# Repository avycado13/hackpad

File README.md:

# hackpad
my hackpad that i can use for various controls

## Features
- 15 buttons in a 3x5 matrix
- 3 rotary encoders for controls like volume and numeric input
- an oled screen to show preset in action and other details
- 3 status leds
- maybe games on the device itself?

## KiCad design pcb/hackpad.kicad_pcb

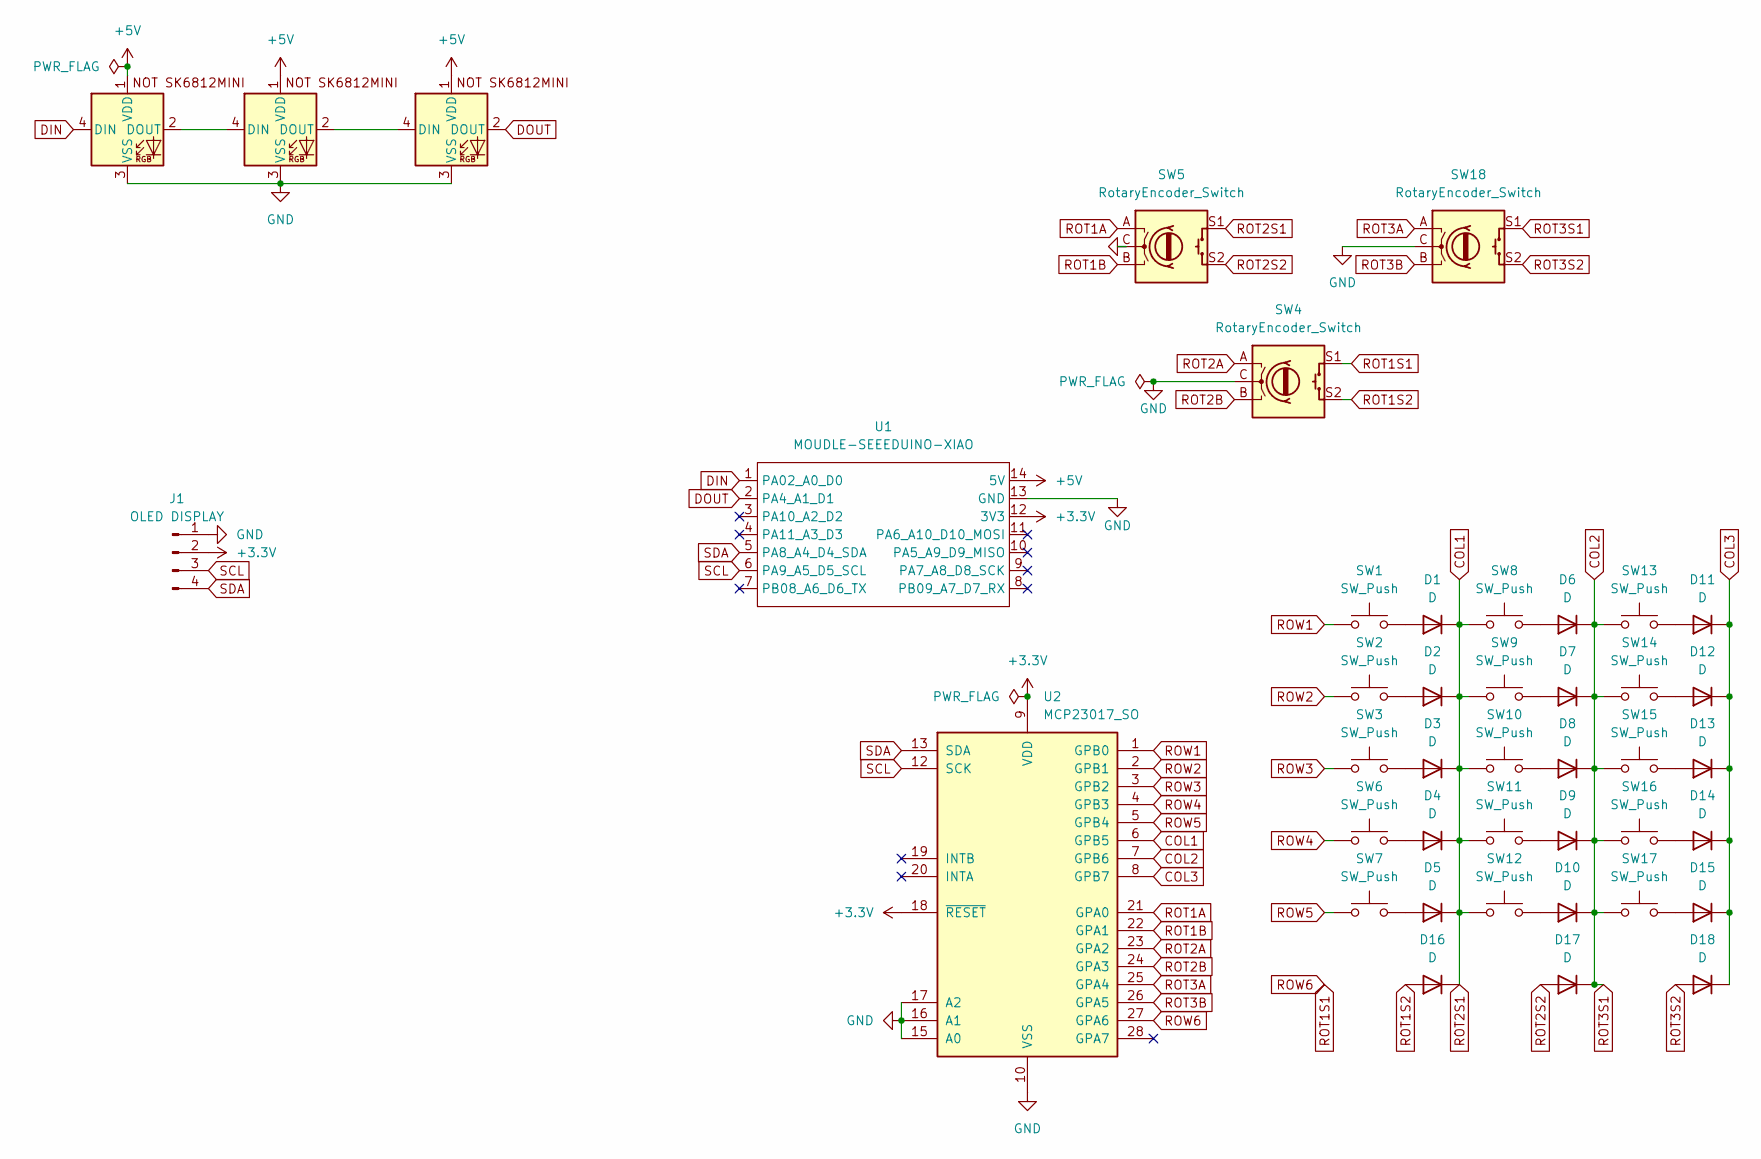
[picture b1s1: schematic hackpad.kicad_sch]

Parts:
D1, D2, D3, D4, D5, D6, D7, D8, D9, D10, D11, D12, D13, D14, D15, D16, D17, D18: D; D_DO-35_SOD27_P7.62mm_Horizontal
D19, D20, D21: SK6812MINI-E; SK6812MINI-E_fixed
J1: OLED DISPLAY; SSD1306-0.91-OLED-4pin-128x32
SW1, SW2, SW3, SW6, SW7, SW8, SW9, SW10, SW11, SW12, SW13, SW14, SW15, SW16, SW17: SW_Push; SW_Cherry_MX_1.00u_PCB
SW4, SW5, SW18: RotaryEncoder_Switch; RotaryEncoder_Alps_EC11E-Switch_Vertical_H20mm
U1: MOUDLE-SEEEDUINO-XIAO; XIAO-Generic-Hybrid-14P-2.54-21X17.8MM
U2: MCP23017_SO; SOIC-28W_7.5x17.9mm_P1.27mm

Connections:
+3.3V: J1.2, U1.12 (3V3), U2.9 (VDD), U2.18 (~RESET)
+5V: D19.1 (VDD), D20.1 (VDD), D21.1 (VDD), U1.14 (5V)
COL1: D1.1 (K), D2.1 (K), D3.1 (K), D4.1 (K), D5.1 (K), D16.1 (K), SW5.S1, SW8.1, SW9.1, SW10.1, SW11.1, SW12.1, U2.6 (GPB5)
COL2: D6.1 (K), D7.1 (K), D8.1 (K), D9.1 (K), D10.1 (K), D17.1 (K), SW13.1, SW14.1, SW15.1, SW16.1, SW17.1, SW18.S1, U2.7 (GPB6)
COL3: D11.1 (K), D12.1 (K), D13.1 (K), D14.1 (K), D15.1 (K), D18.1 (K), U2.8 (GPB7)
DIN: D19.4 (DIN), U1.1 (PA02_A0_D0)
DOUT: D21.2 (DOUT), U1.2 (PA4_A1_D1)
GND: D19.3 (VSS), D20.3 (VSS), D21.3 (VSS), J1.1, SW4.C, SW5.C, SW18.C, U1.13 (GND), U2.10 (VSS), U2.15 (A0), U2.16 (A1), U2.17 (A2)
unnamed: D1.2 (A), SW1.2
unnamed: D2.2 (A), SW2.2
unnamed: D3.2 (A), SW3.2
unnamed: D4.2 (A), SW6.2
unnamed: D5.2 (A), SW7.2
unnamed: D6.2 (A), SW8.2
unnamed: D7.2 (A), SW9.2
unnamed: D8.2 (A), SW10.2
unnamed: D9.2 (A), SW11.2
unnamed: D10.2 (A), SW12.2
unnamed: D11.2 (A), SW13.2
unnamed: D12.2 (A), SW14.2
unnamed: D13.2 (A), SW15.2
unnamed: D14.2 (A), SW16.2
unnamed: D15.2 (A), SW17.2
unnamed: D19.2 (DOUT), D20.4 (DIN)
unnamed: D20.2 (DOUT), D21.4 (DIN)
ROT1A: SW5.A, U2.21 (GPA0)
ROT1B: SW5.B, U2.22 (GPA1)
ROT1S1: SW4.S1, U2.27 (GPA6)
ROT1S2: D16.2 (A), SW4.S2
ROT2A: SW4.A, U2.23 (GPA2)
ROT2B: SW4.B, U2.24 (GPA3)
ROT2S2: D17.2 (A), SW5.S2
ROT3A: SW18.A, U2.25 (GPA4)
ROT3B: SW18.B, U2.26 (GPA5)
ROT3S2: D18.2 (A), SW18.S2
ROW1: SW1.1, U2.1 (GPB0)
ROW2: SW2.1, U2.2 (GPB1)
ROW3: SW3.1, U2.3 (GPB2)
ROW4: SW6.1, U2.4 (GPB3)
ROW5: SW7.1, U2.5 (GPB4)
SCL: J1.3, U1.6 (PA9_A5_D5_SCL), U2.12 (SCK)
SDA: J1.4, U1.5 (PA8_A4_D4_SDA), U2.13 (SDA)

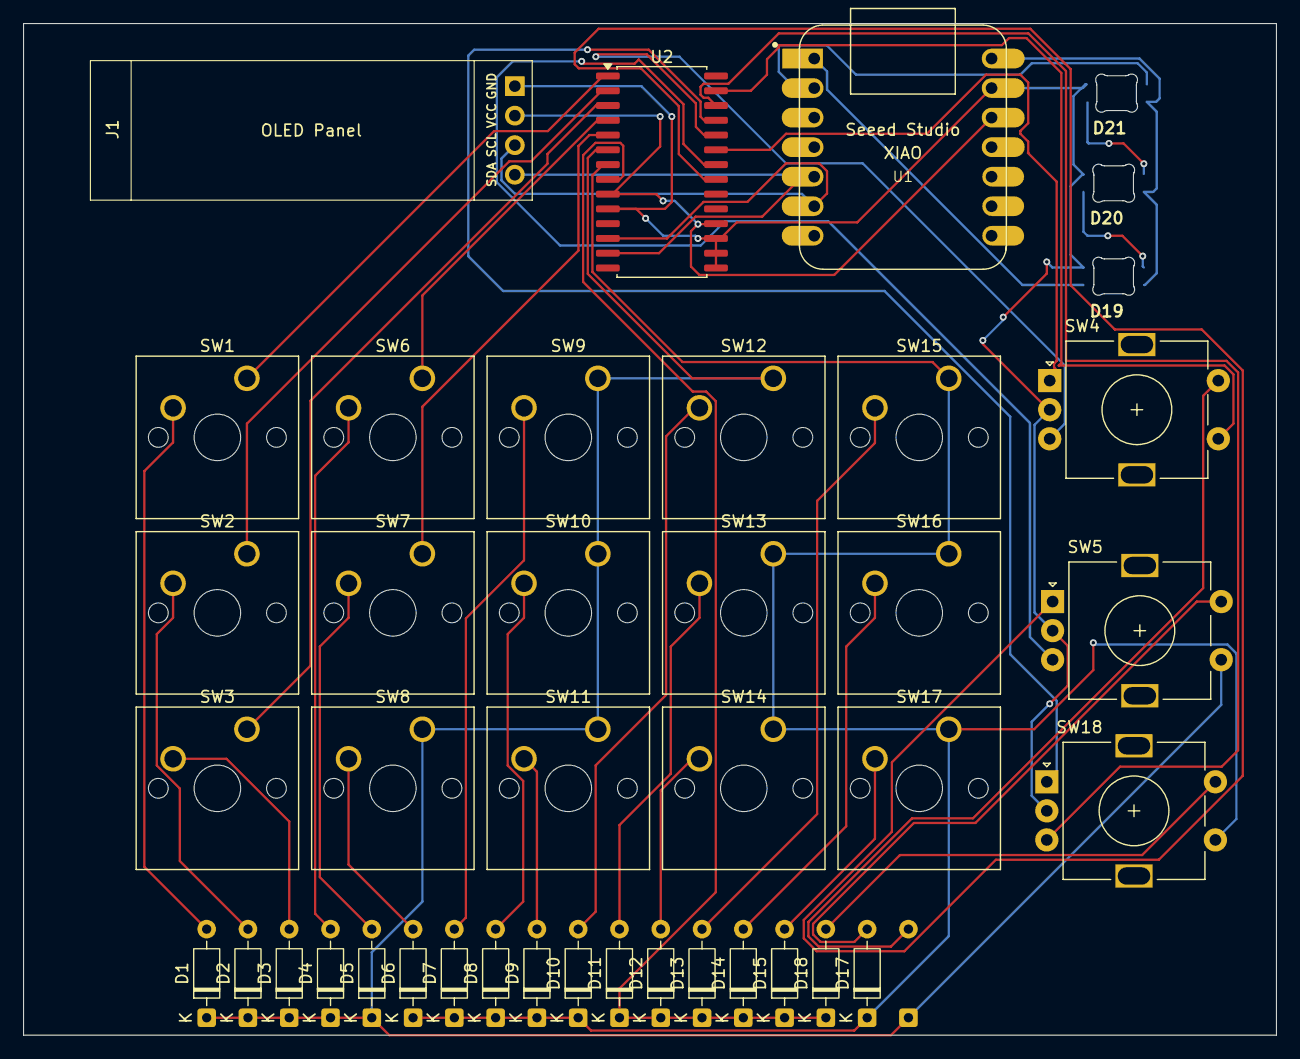
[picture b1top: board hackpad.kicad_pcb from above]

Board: 2 copper layers, 107.8 x 87.0 mm, 42 parts (1 on the bottom side), 42 nets.
